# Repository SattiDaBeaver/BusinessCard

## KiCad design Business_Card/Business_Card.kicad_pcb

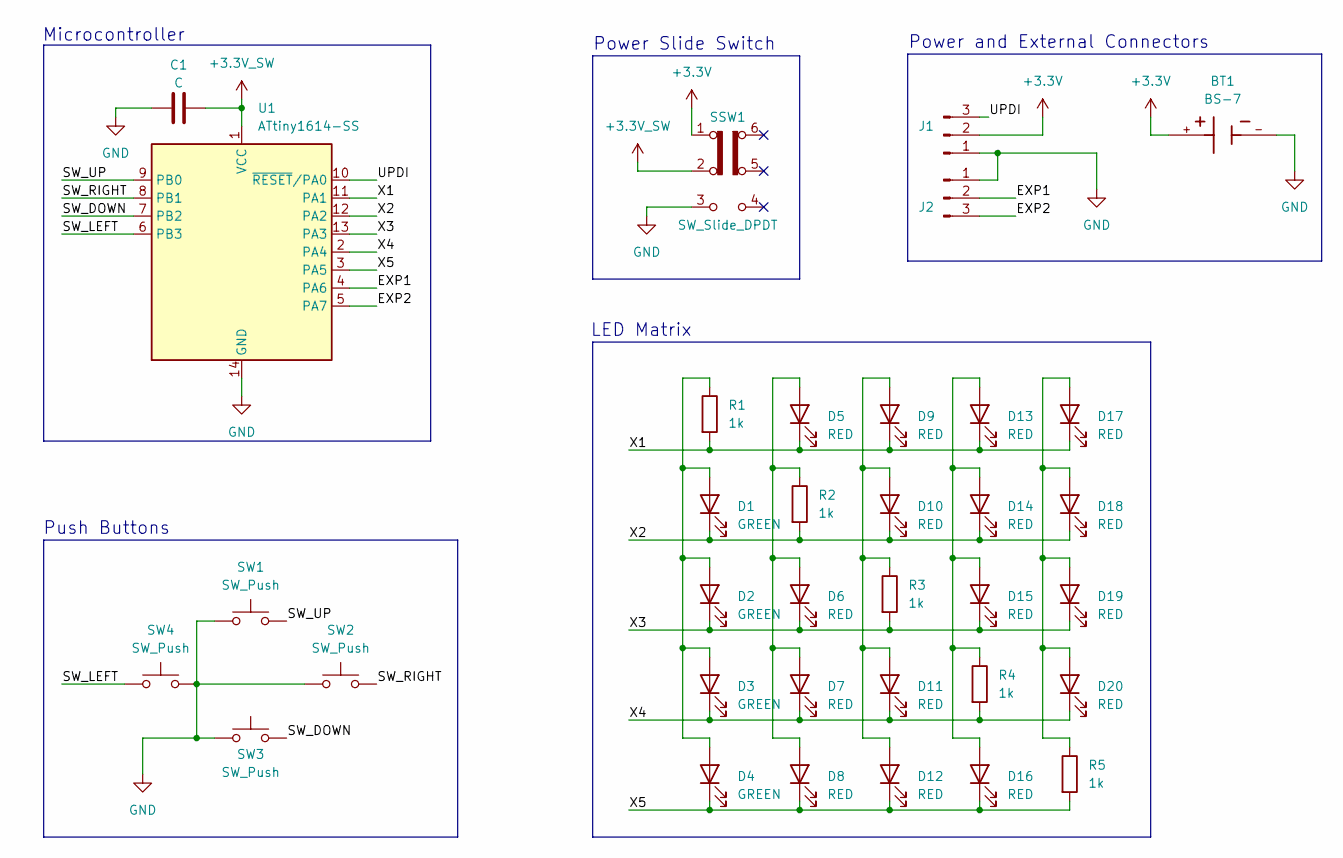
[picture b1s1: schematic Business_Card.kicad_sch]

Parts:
BT1: BS-7; battery_holder; PARTREV H
C1: C; C_0805_2012Metric_Pad1.18x1.45mm_HandSolder
D1, D2, D3, D4: GREEN; LED_1206-0603_Morph
D5, D6, D7, D8, D9, D10, D11, D12, D13, D14, D15, D16, D17, D18, D19, D20: RED; LED_1206-0603_Morph
J1, J2: External_Headers; ExternalHeader_3pin; MPN 0022272031
R1, R2, R3, R4, R5: 1k; R_0603_1608Metric_Pad0.98x0.95mm_HandSolder
SSW1: SW_Slide_DPDT; slide_switch_fp
SW1, SW2, SW3, SW4: SW_Push; push_button
U1: ATtiny1614-SS; SOIC-14_3.9x8.7mm_P1.27mm

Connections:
+3.3V: BT1.+, J1.2, SSW1.1 (A)
+3.3V_SW: C1.2, SSW1.2 (B), U1.1 (VCC)
/EXP1: J2.2, U1.4 (PA6)
/EXP2: J2.3, U1.5 (PA7)
/SW_DOWN: SW3.2, U1.7 (PB2)
/SW_LEFT: SW4.1, U1.6 (PB3)
/SW_RIGHT: SW2.2, U1.8 (PB1)
/SW_UP: SW1.2, U1.9 (PB0)
/UPDI: J1.3, U1.10 (~RESET/PA0)
/X1: D5.1 (K), D9.1 (K), D13.1 (K), D17.1 (K), R1.2, U1.11 (PA1)
/X2: D1.1 (K), D10.1 (K), D14.1 (K), D18.1 (K), R2.2, U1.12 (PA2)
/X3: D2.1 (K), D6.1 (K), D15.1 (K), D19.1 (K), R3.2, U1.13 (PA3)
/X4: D3.1 (K), D7.1 (K), D11.1 (K), D20.1 (K), R4.2, U1.2 (PA4)
/X5: D4.1 (K), D8.1 (K), D12.1 (K), D16.1 (K), R5.2, U1.3 (PA5)
GND: BT1.-, C1.1, J1.1, J2.1, SSW1.3 (C), SW1.1, SW2.1, SW3.1, SW4.2, U1.14 (GND)
unnamed: D1.2 (A), D2.2 (A), D3.2 (A), D4.2 (A), R1.1
unnamed: D5.2 (A), D6.2 (A), D7.2 (A), D8.2 (A), R2.1
unnamed: D9.2 (A), D10.2 (A), D11.2 (A), D12.2 (A), R3.1
unnamed: D13.2 (A), D14.2 (A), D15.2 (A), D16.2 (A), R4.1
unnamed: D17.2 (A), D18.2 (A), D19.2 (A), D20.2 (A), R5.1

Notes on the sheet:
Push Buttons
LED Matrix
Microcontroller
Power Slide Switch
Power and External Connectors

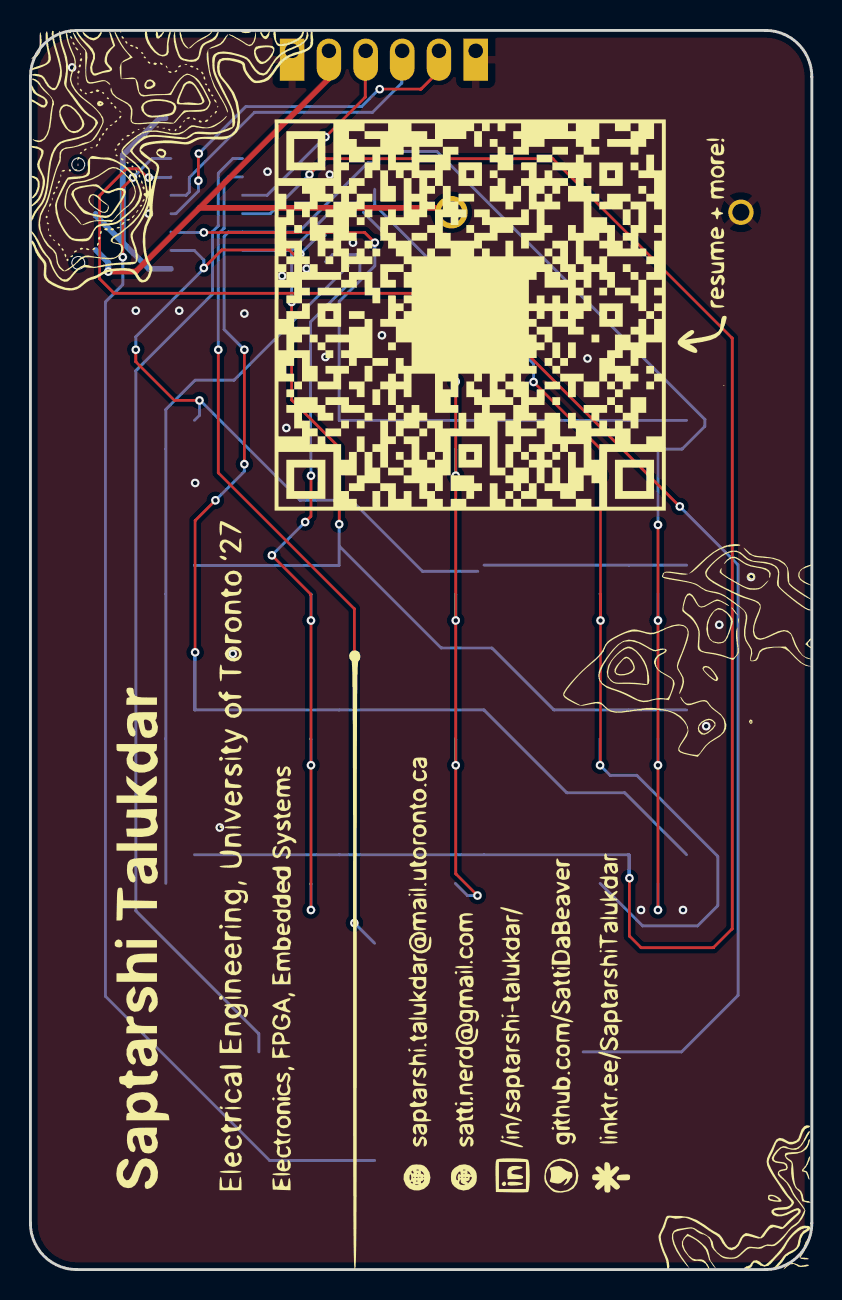
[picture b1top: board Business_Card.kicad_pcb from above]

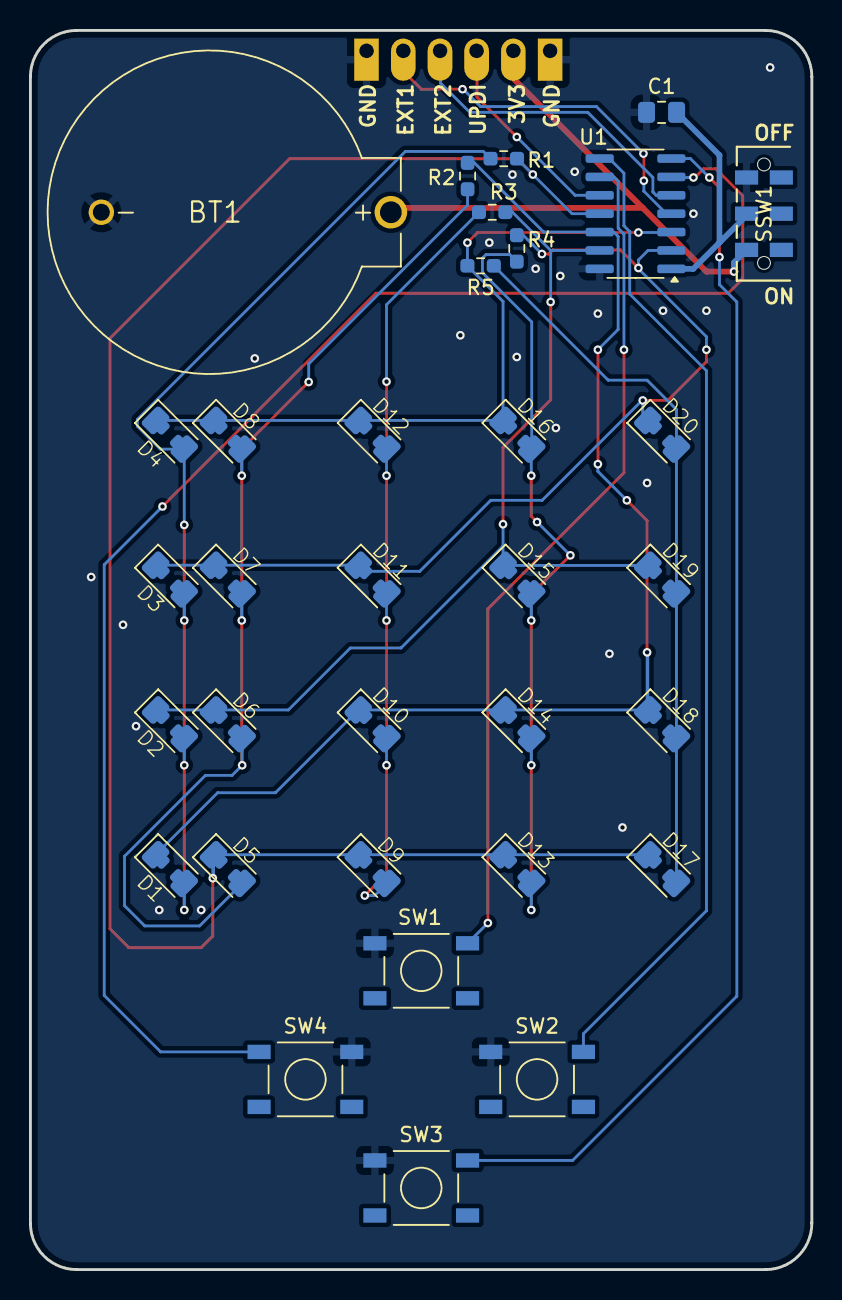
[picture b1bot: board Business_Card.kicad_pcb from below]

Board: 2 copper layers, 54.0 x 85.6 mm, 36 parts (34 on the bottom side), 20 nets.

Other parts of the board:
P75: LOGO; FrontPage80

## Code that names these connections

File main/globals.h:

#ifndef GLOBALS_H
#define GLOBALS_H

#include <stdint.h>

#define OUTPUT_PIN_NUM      5

#define X1                  1
#define X2                  2
#define X3                  3
#define X4                  4
#define X5                  5

#define NO_INPUT            0x0
#define IN_UP               0x1
#define IN_RIGHT            0x2
#define IN_DOWN             0x4
#define IN_LEFT             0x8

#define SW_UP               0
#define SW_RIGHT            1
#define SW_DOWN             2
#define SW_LEFT             3

#define EXT1                6
#define EXT2                7

#define OBSTACLE            1
#define NO_OBSTACLE         0

#define DIR_UP              1
#define DIR_DOWN            -1

#endif

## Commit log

2025-06-13 added shift lane and random lanes
2025-06-13 fixed random lanes to give gaps in upper row
2025-06-13 changed initial grid array
2025-06-13 completed a basic version of the game
2025-08-30 fixed schematic spacing
